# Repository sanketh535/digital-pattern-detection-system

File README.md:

DIGITAL PATTERN DETECTION SYSTEM USING SEQUENTIAL LOGIC (1011)

PROJECT OVERVIEW

This project involves the design and implementation of a digital pattern detection system using sequential logic circuits. The system is designed to detect the assigned 4-bit binary sequence 1011.

The complete system consists of three main sections:

1. Random Pattern Generator – Generates 4-bit binary patterns.
2. PISO Shift Register – Loads parallel data and converts it into a serial data stream.
3. FSM Pattern Detector – Detects the binary sequence 1011 from the incoming serial data.

The three sections are integrated using a common clock signal to perform sequential pattern detection.

SYSTEM ARCHITECTURE

1. Random Pattern Generator
2. Parallel-In Serial-Out (PISO) Shift Register
3. Finite State Machine (FSM) Pattern Detector
4. Complete Integrated Pattern Detection System

TOOLS AND TECHNOLOGIES

- Proteus – Circuit design and simulation
- KiCad – PCB design
- Sequential Logic Circuits
- Shift Registers
- Finite State Machines (FSM)

REPOSITORY CONTENTS

Proteus:
- Complete integrated system simulation
- Random Pattern Generator simulation
- PISO Shift Register simulation
- FSM Pattern Detector simulation

KiCad:
- Random Pattern Generator PCB design
- PISO Shift Register PCB design
- FSM Pattern Detector PCB design

Images:
- KiCad 3D PCB design views
- Photographs of the three fabricated PCBs

Documentation:
- Project assignment report

PCB DESIGN AND FABRICATION

PCB layouts were designed using KiCad for all three sections of the system. Three PCBs were subsequently fabricated based on the designs.

Note: The fabricated PCBs are bare boards, and electronic components have not yet been mounted.

KEY LEARNING OUTCOMES

- Digital system design using sequential logic
- Shift register design and operation
- Finite State Machine design for sequence detection
- Circuit simulation using Proteus
- PCB layout design using KiCad
- Practical experience in PCB fabrication

PROJECT TEAM

This project was completed collaboratively as part of an academic assignment.

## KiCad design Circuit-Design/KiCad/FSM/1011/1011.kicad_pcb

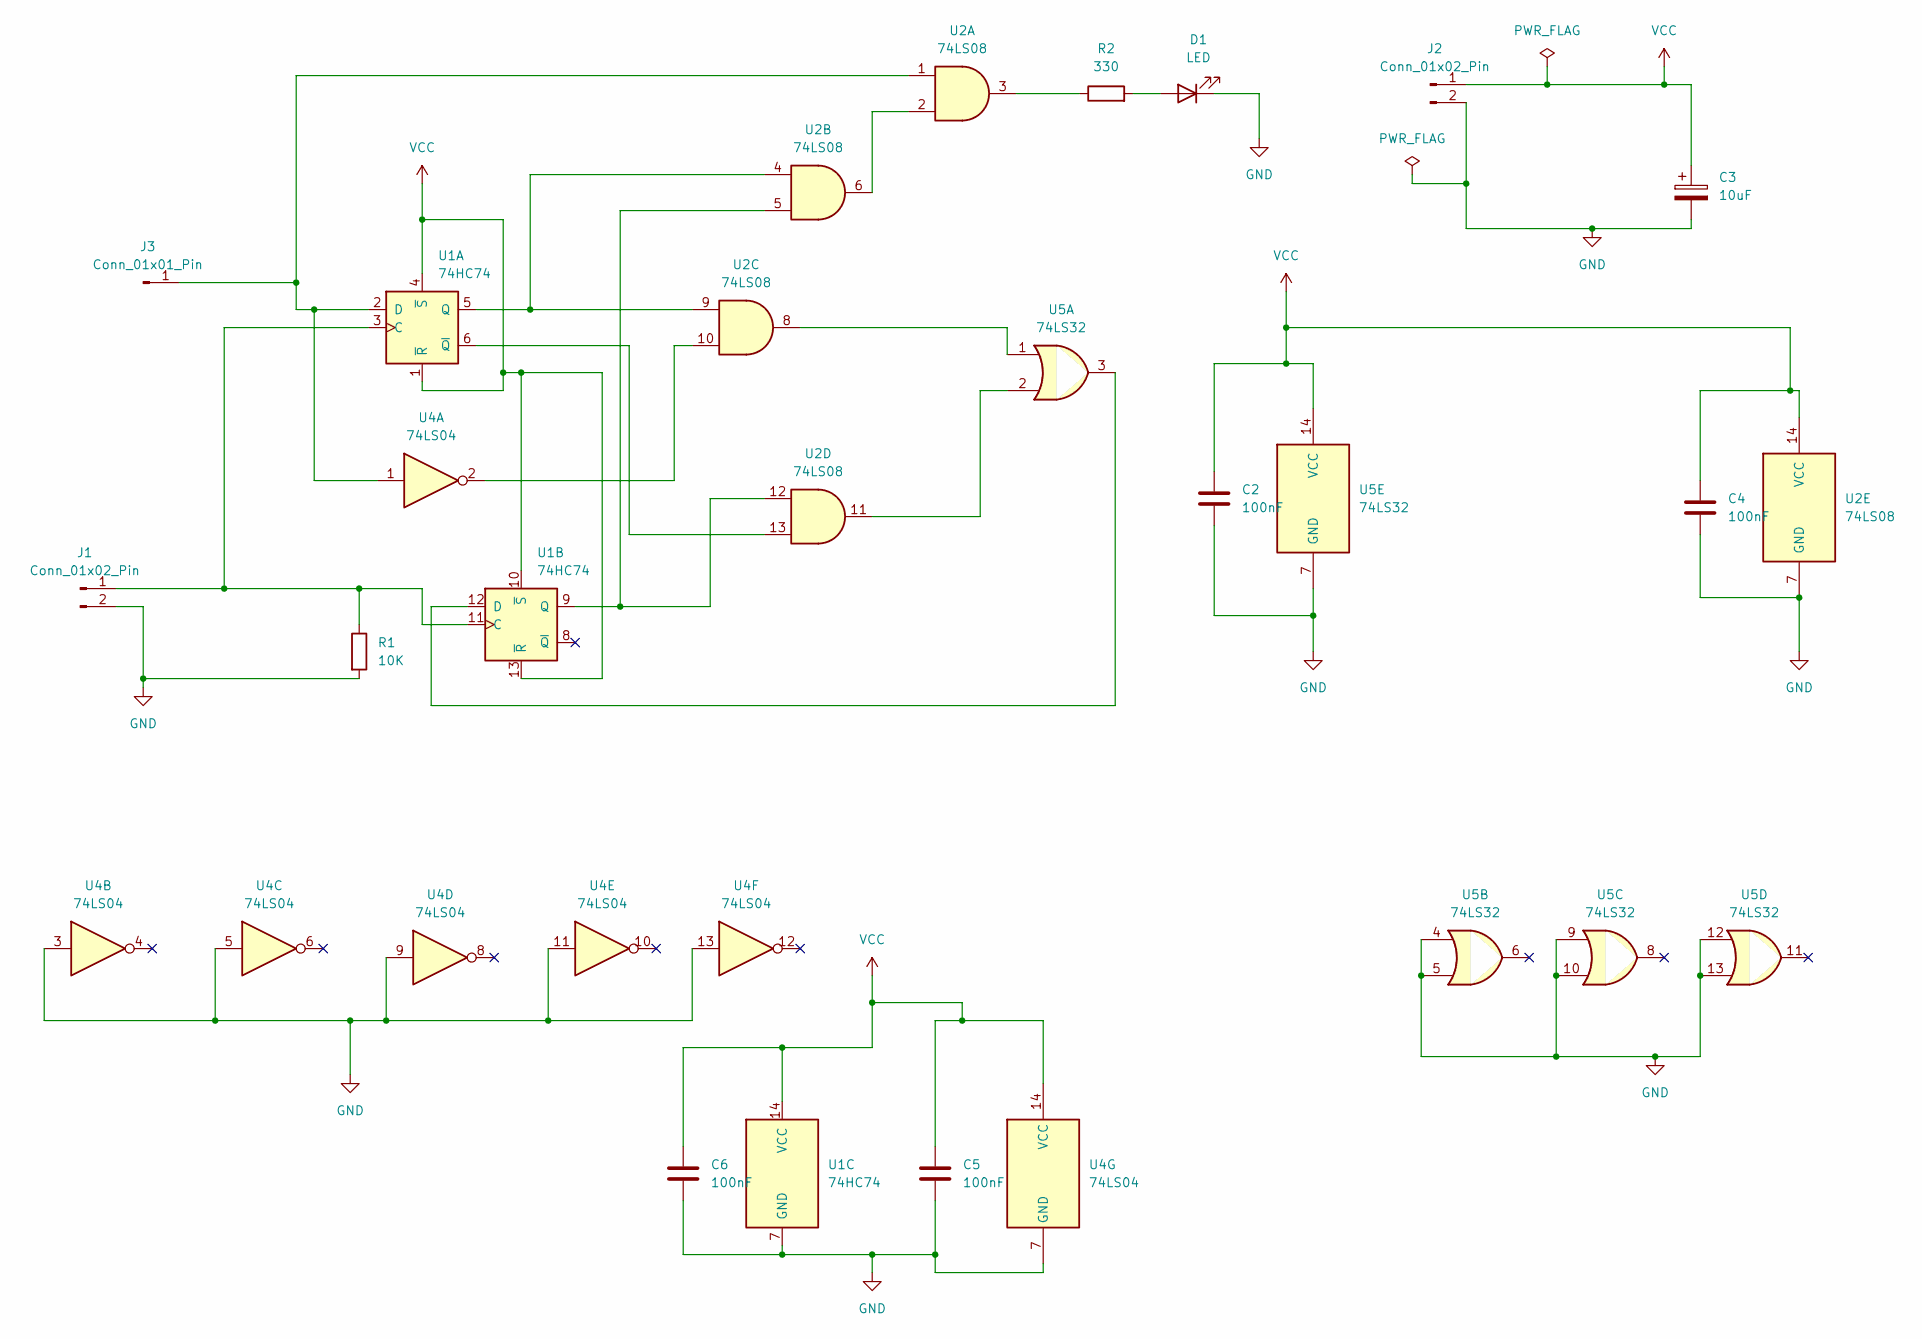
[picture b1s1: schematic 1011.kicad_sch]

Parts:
C2, C4, C5, C6: 100nF; C_Disc_D5.0mm_W2.5mm_P5.00mm
C3: 10uF; CP_Radial_D5.0mm_P2.00mm
D1: LED; LED_D5.0mm
J1, J2: Conn_01x02_Pin; PinHeader_1x02_P2.54mm_Vertical
J3: Conn_01x01_Pin; PinHeader_1x01_P2.54mm_Vertical
R1: 10K; R_Axial_DIN0207_L6.3mm_D2.5mm_P7.62mm_Horizontal
R2: 330; R_Axial_DIN0207_L6.3mm_D2.5mm_P7.62mm_Horizontal
U1: 74HC74; DIP-14_W7.62mm
U2: 74LS08; DIP-14_W7.62mm
U4: 74LS04; DIP-14_W7.62mm
U5: 74LS32; DIP-14_W7.62mm

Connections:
GND: C2.2, C3.2, C4.2, C5.2, C6.2, D1.1 (K), J1.2, J2.2, R1.2, U1.7 (GND), U2.7 (GND), U4.3, U4.5, U4.7 (GND), U4.9, U4.11, U4.13, U5.4, U5.5, U5.7 (GND), U5.9, U5.10, U5.12, U5.13
unnamed: D1.2 (A), R2.2
unnamed: J1.1, R1.1, U1.3 (C), U1.11 (C)
unnamed: J3.1 (Pin_1_1), U1.2 (D), U2.1, U4.1
unnamed: R2.1, U2.3
unnamed: U1.5 (Q), U2.4, U2.9
unnamed: U1.6 (~Q), U2.13
unnamed: U1.12 (D), U5.3
unnamed: U1.9 (Q), U2.5, U2.12
unnamed: U2.2, U2.6
unnamed: U2.8, U5.1
unnamed: U2.10, U4.2
unnamed: U2.11, U5.2
VCC: C2.1, C3.1, C4.1, C5.1, C6.1, J2.1, U1.1 (~R), U1.4 (~S), U1.10 (~S), U1.13 (~R), U1.14 (VCC), U2.14 (VCC), U4.14 (VCC), U5.14 (VCC)

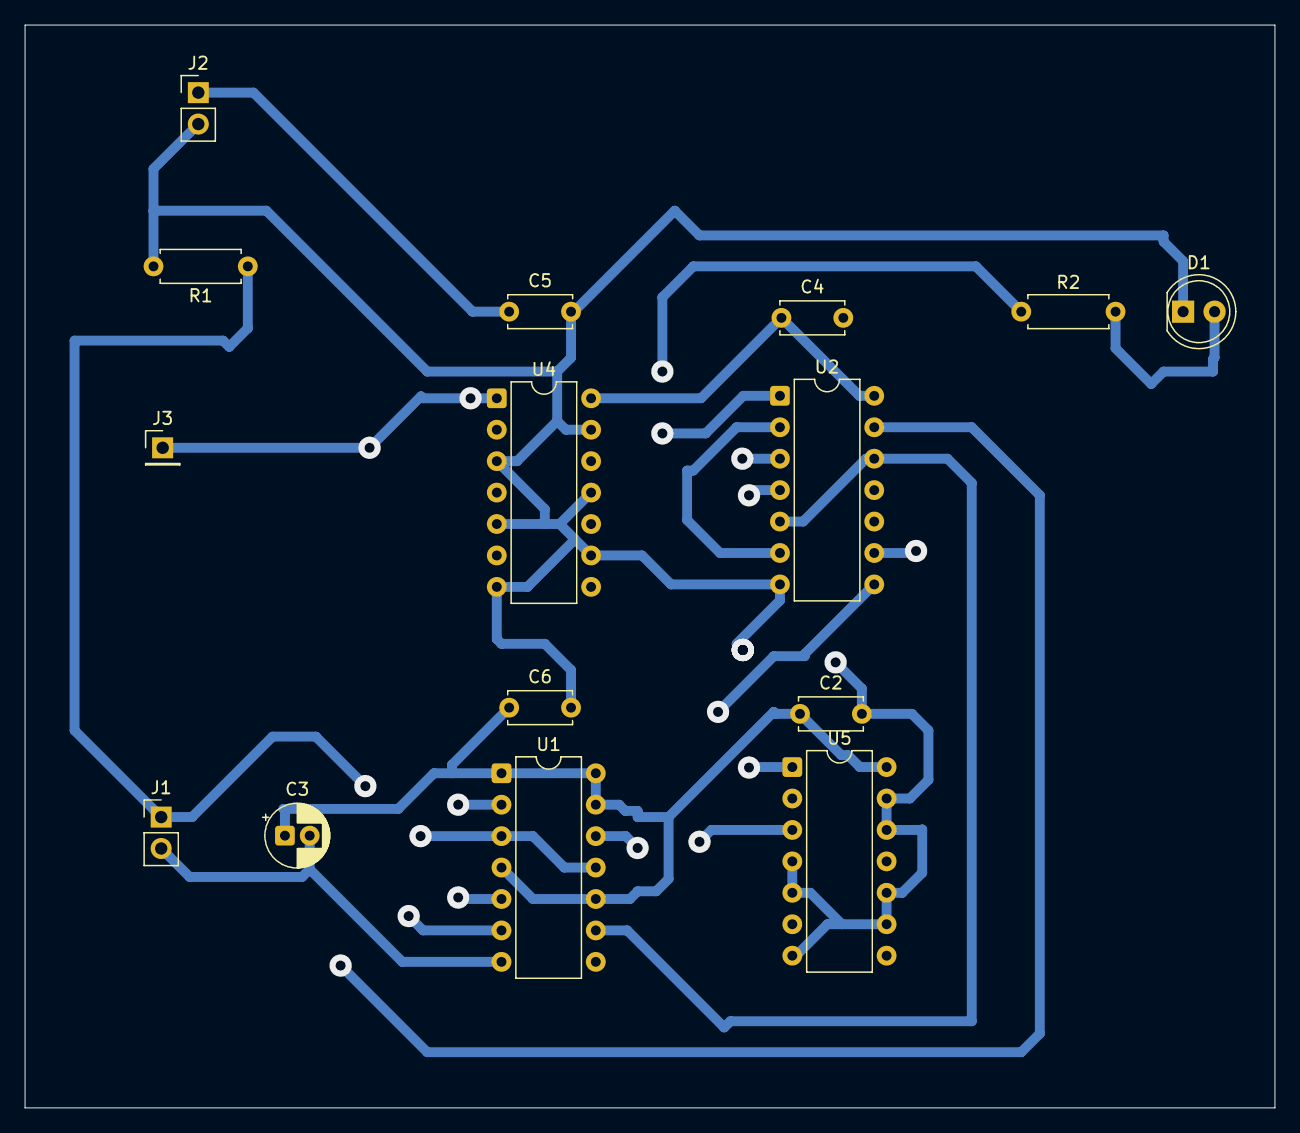
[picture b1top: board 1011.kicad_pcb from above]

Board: 2 copper layers, 101.0 x 87.5 mm, 15 parts (0 on the bottom side), 14 nets.

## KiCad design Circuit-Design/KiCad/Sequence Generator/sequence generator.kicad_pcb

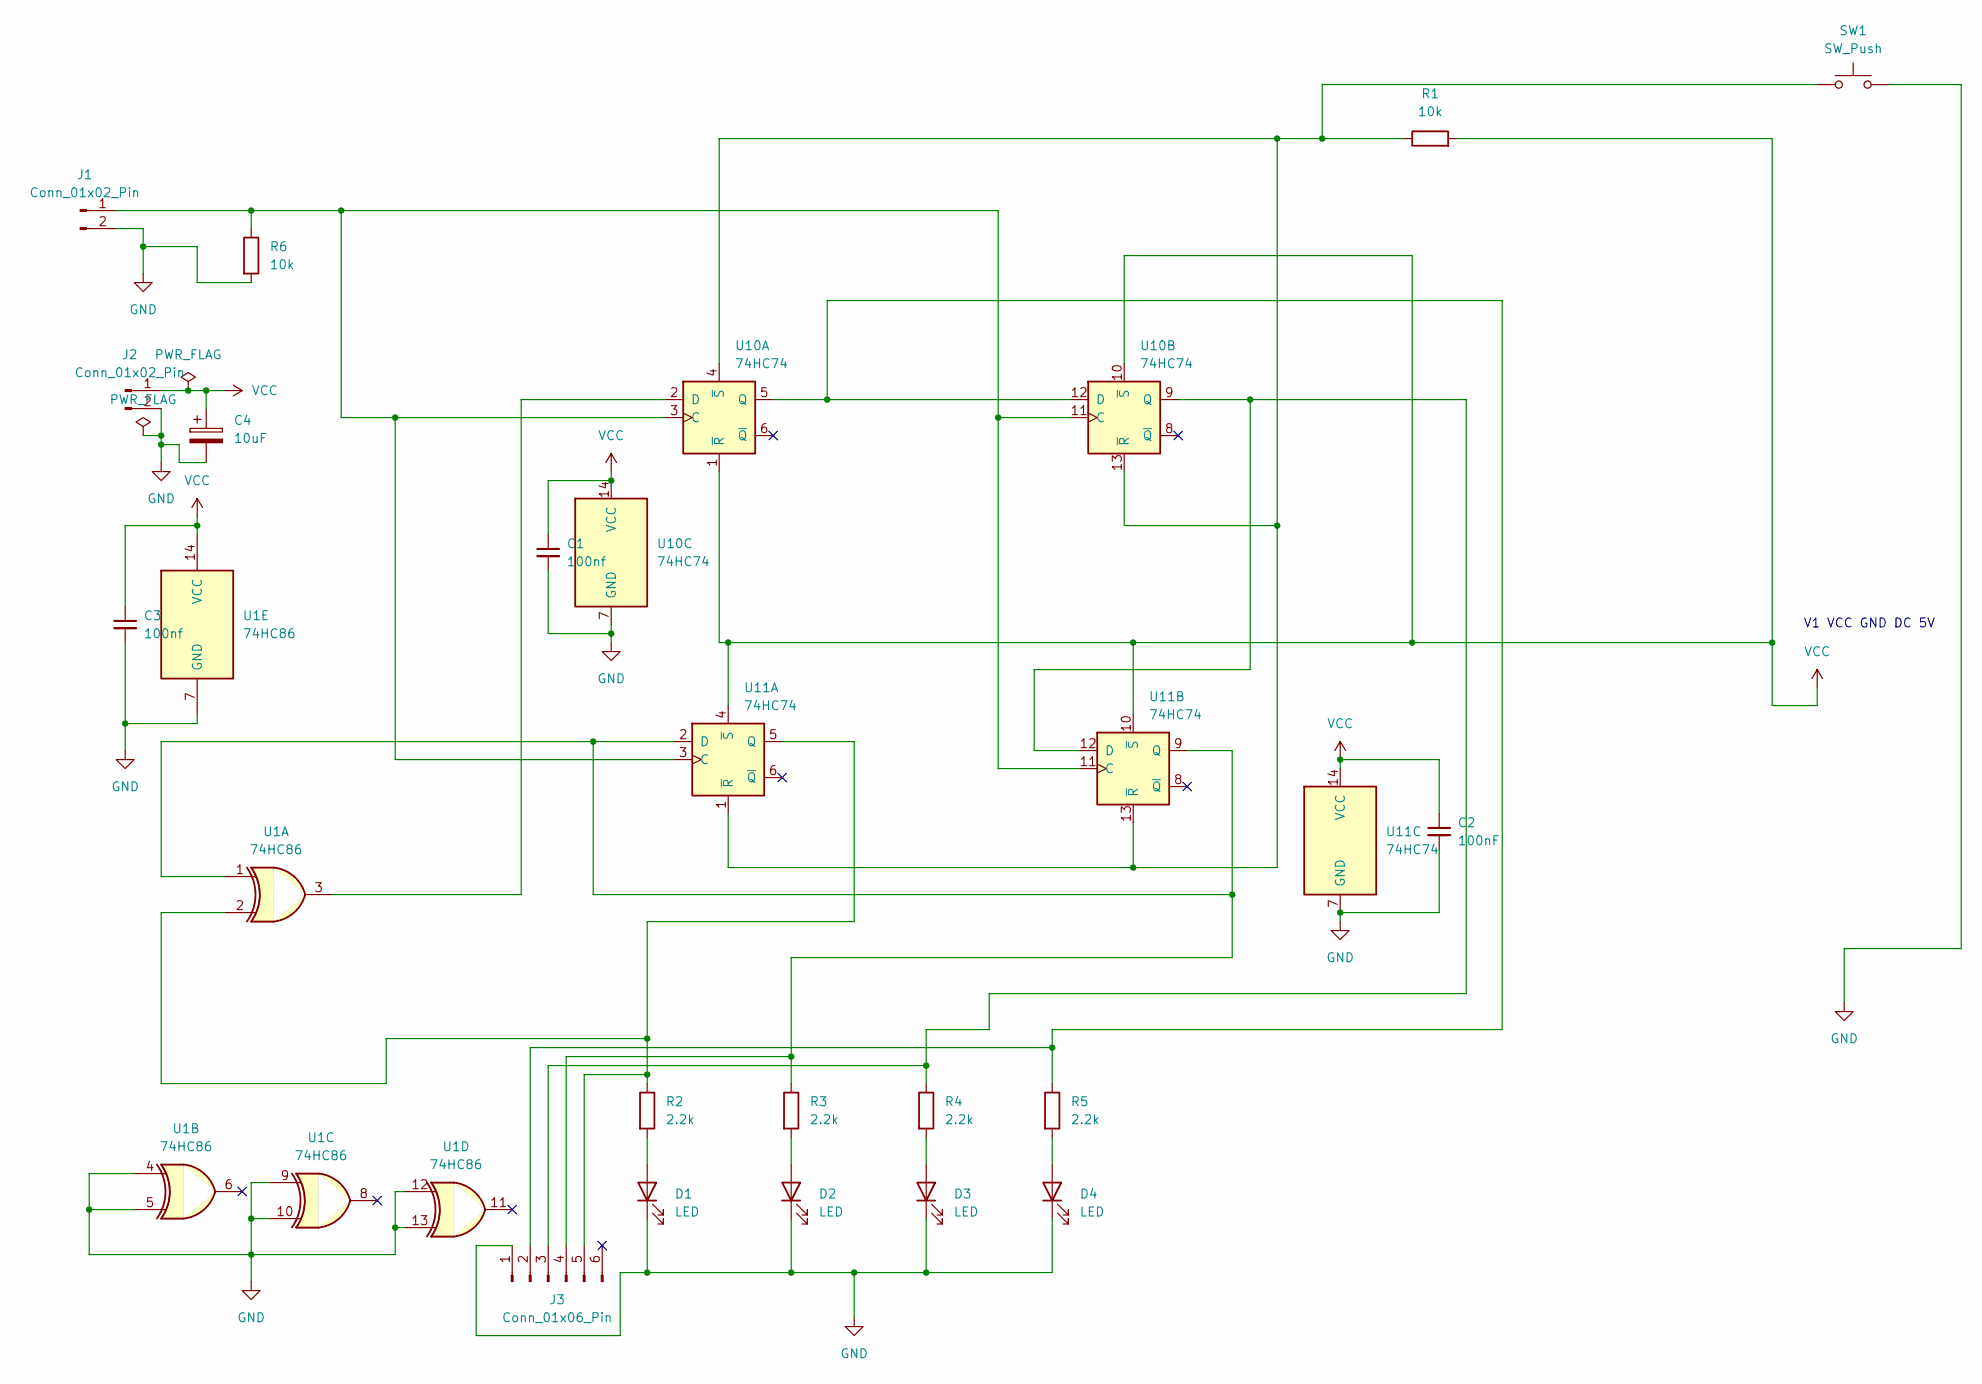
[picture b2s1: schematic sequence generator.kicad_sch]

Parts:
C1, C3: 100nf; C_Disc_D5.0mm_W2.5mm_P5.00mm
C2: 100nF; C_Disc_D5.0mm_W2.5mm_P5.00mm
C4: 10uF; C_Disc_D5.0mm_W2.5mm_P5.00mm
D1, D2, D3, D4: LED; LED_D5.0mm
J1, J2: Conn_01x02_Pin; PinHeader_1x02_P2.54mm_Vertical
J3: Conn_01x06_Pin; PinHeader_1x06_P2.54mm_Vertical
R1, R6: 10k; R_Axial_DIN0207_L6.3mm_D2.5mm_P10.16mm_Horizontal
R2, R3, R4, R5: 2.2k; R_Axial_DIN0207_L6.3mm_D2.5mm_P10.16mm_Horizontal
SW1: SW_Push; SW_PUSH_6mm
U1: 74HC86; DIP-14_W7.62mm
U10, U11: 74HC74; DIP-14_W7.62mm

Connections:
GND: C1.2, C2.2, C3.2, C4.2, D1.1 (K), D2.1 (K), D3.1 (K), D4.1 (K), J1.2, J2.2, J3.1, R6.2, SW1.2, U1.4, U1.5, U1.7 (GND), U1.9, U1.10, U1.12, U1.13, U10.7 (GND), U11.7 (GND)
unnamed: D1.2 (A), R2.2
unnamed: D2.2 (A), R3.2
unnamed: D3.2 (A), R4.2
unnamed: D4.2 (A), R5.2
unnamed: J1.1, R6.1, U10.3 (C), U10.11 (C), U11.3 (C), U11.11 (C)
unnamed: J3.2, R5.1, U10.5 (Q), U10.12 (D)
unnamed: J3.3, R4.1, U10.9 (Q), U11.12 (D)
unnamed: J3.4, R3.1, U1.1, U11.2 (D), U11.9 (Q)
unnamed: J3.5, R2.1, U1.2, U11.5 (Q)
unnamed: U1.3, U10.2 (D)
unnamed: R1.1, SW1.1, U10.4 (~S), U10.13 (~R), U11.1 (~R), U11.13 (~R)
VCC: C1.1, C2.1, C3.1, C4.1, J2.1, R1.2, U1.14 (VCC), U10.1 (~R), U10.10 (~S), U10.14 (VCC), U11.4 (~S), U11.10 (~S), U11.14 (VCC)

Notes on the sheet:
V1 VCC GND DC 5V

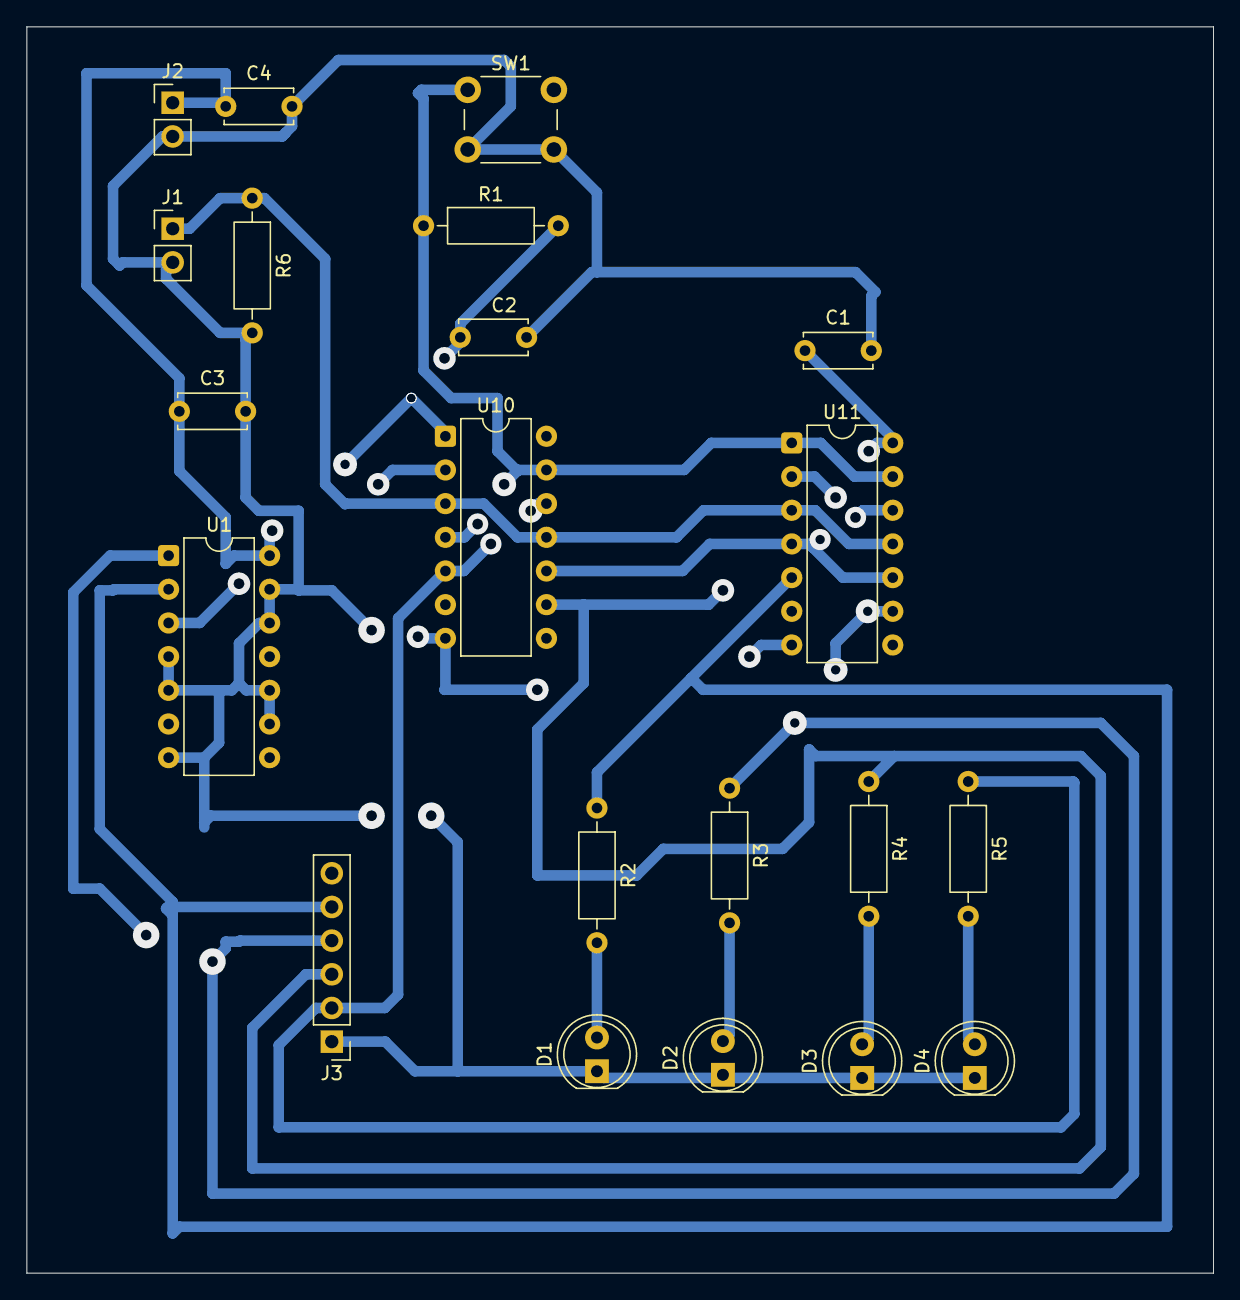
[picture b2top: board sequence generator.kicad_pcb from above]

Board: 2 copper layers, 89.5 x 94.0 mm, 21 parts (0 on the bottom side), 13 nets.

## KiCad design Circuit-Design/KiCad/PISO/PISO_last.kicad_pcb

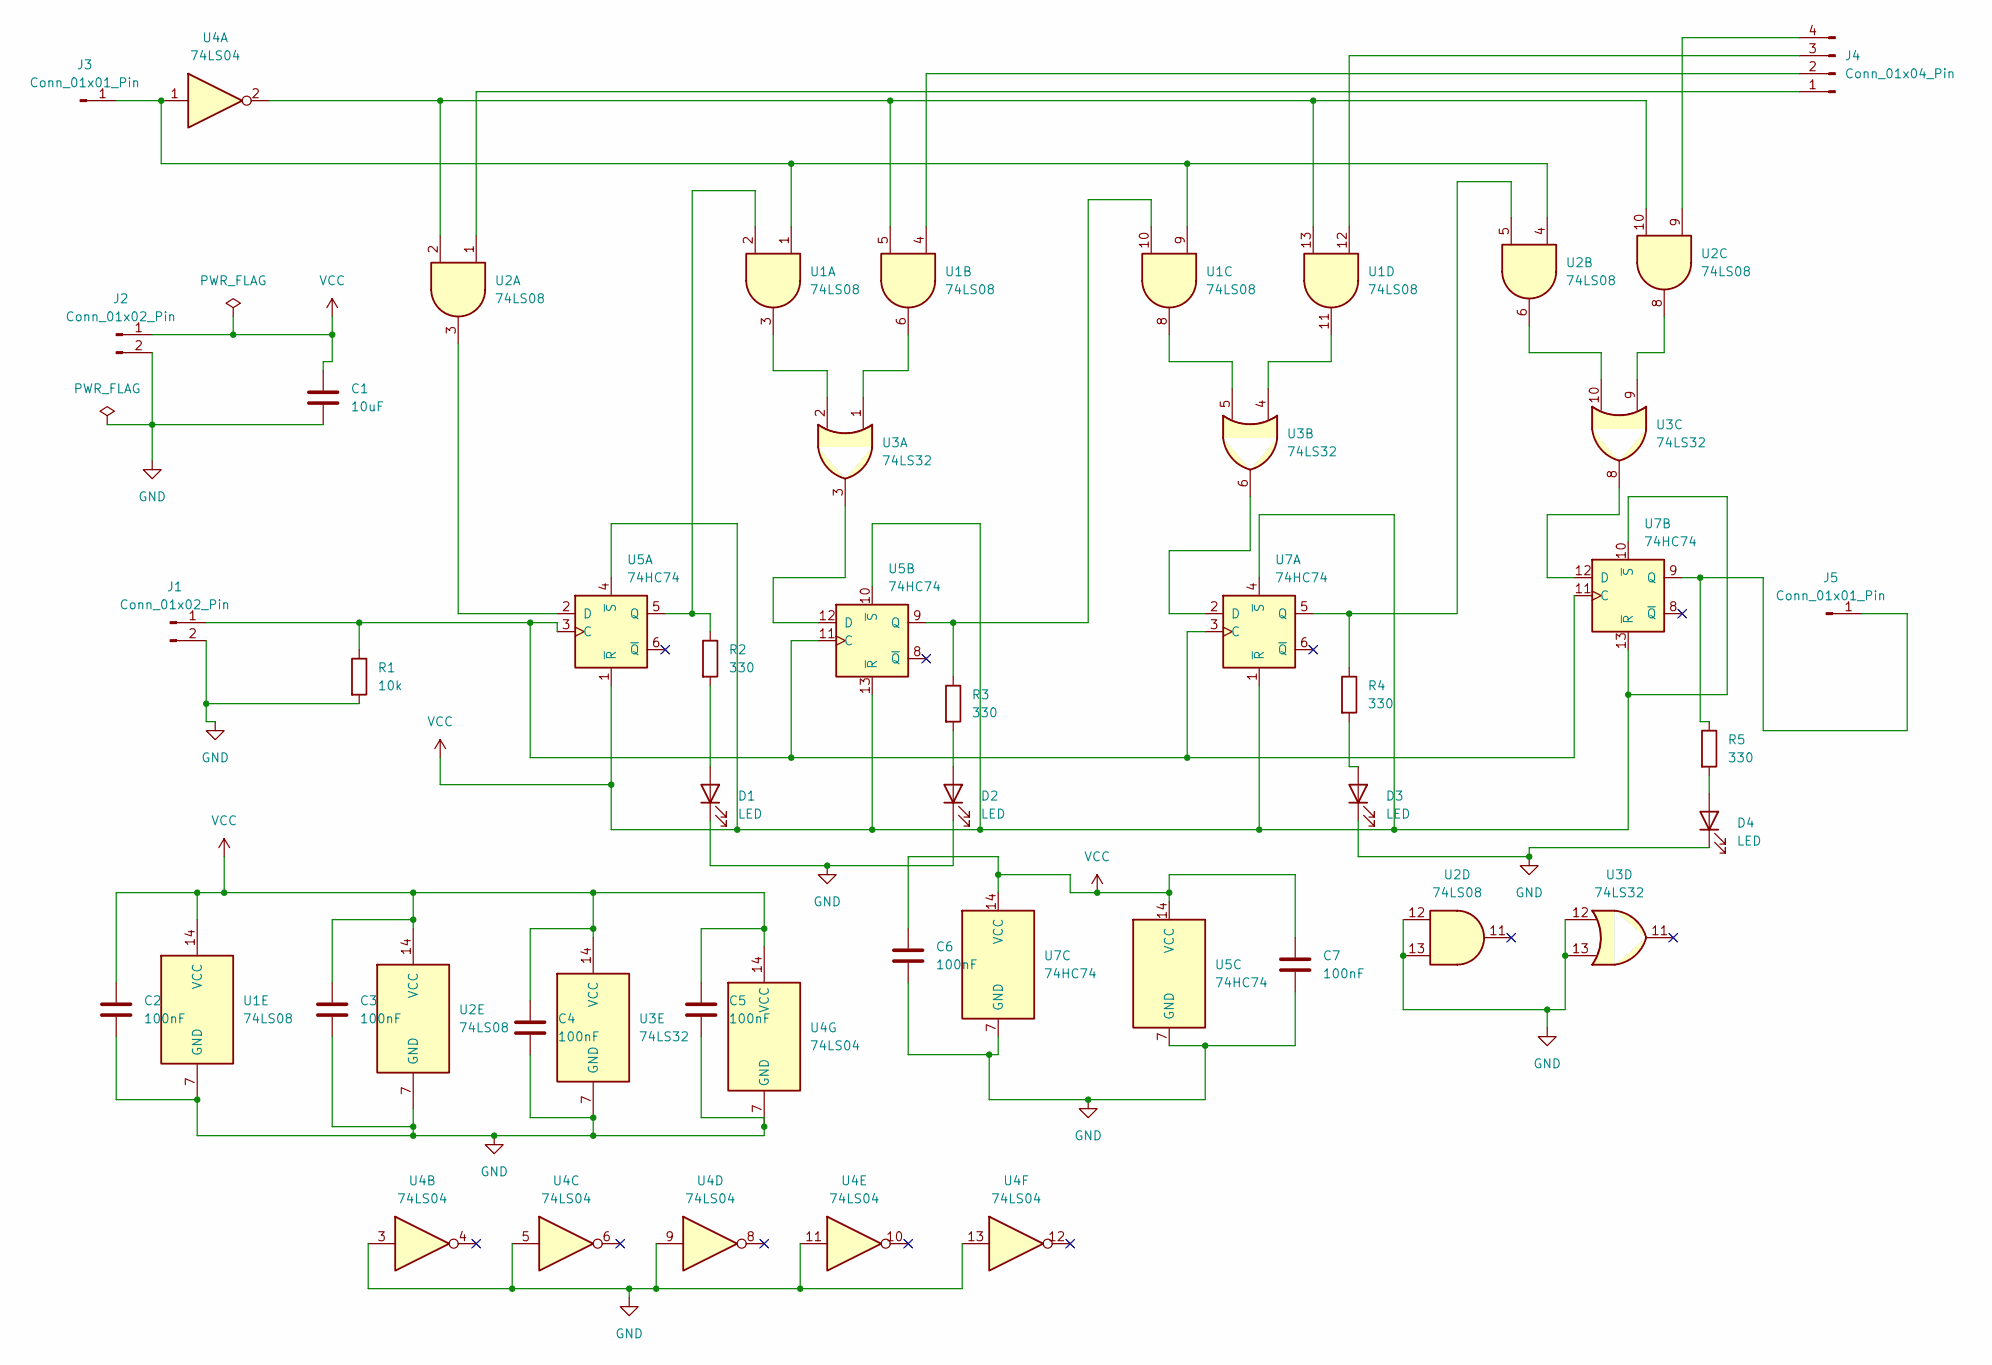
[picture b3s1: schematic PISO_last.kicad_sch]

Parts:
C1: 10uF
C2, C3, C4, C5, C6, C7: 100nF
D1, D2, D3, D4: LED; LED_D5.0mm
J1, J2: Conn_01x02_Pin
J3, J5: Conn_01x01_Pin
J4: Conn_01x04_Pin
R1: 10k
R2, R3, R4, R5: 330; R_Axial_DIN0207_L6.3mm_D2.5mm_P7.62mm_Horizontal
U1, U2: 74LS08
U3: 74LS32
U4: 74LS04
U5, U7: 74HC74

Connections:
GND: C1.2, C2.2, C3.2, C4.2, C5.2, C6.2, C7.2, D1.1 (K), D2.1 (K), D3.1 (K), D4.1 (K), J1.2, J2.2, R1.2, U1.7 (GND), U2.7 (GND), U2.12, U2.13, U3.7 (GND), U3.12, U3.13, U4.3, U4.5, U4.7 (GND), U4.9, U4.11, U4.13, U5.7 (GND), U7.7 (GND)
unnamed: D1.2 (A), R2.2
unnamed: D2.2 (A), R3.2
unnamed: D3.2 (A), R4.2
unnamed: D4.2 (A), R5.2
unnamed: J1.1, R1.1, U5.3 (C), U5.11 (C), U7.3 (C), U7.11 (C)
unnamed: J3.1 (Pin_1_1), U1.1, U1.9, U2.4, U4.1
unnamed: J4.1, U2.1
unnamed: J4.2, U1.4
unnamed: J4.3, U1.12
unnamed: J4.4, U2.9
unnamed: J5.1 (Pin_1_1), R5.1, U7.9 (Q)
unnamed: U1.3, U3.2
unnamed: U1.6, U3.1
unnamed: U1.8, U3.5
unnamed: U1.11, U3.4
unnamed: U1.5, U1.13, U2.2, U2.10, U4.2
unnamed: U2.6, U3.10
unnamed: U2.8, U3.9
unnamed: U2.3, U5.2 (D)
unnamed: R2.1, U1.2, U5.5 (Q)
unnamed: U3.3, U5.12 (D)
unnamed: R3.1, U1.10, U5.9 (Q)
unnamed: U3.6, U7.2 (D)
unnamed: R4.1, U2.5, U7.5 (Q)
unnamed: U3.8, U7.12 (D)
VCC: C1.1, C2.1, C3.1, C4.1, C5.1, C6.1, C7.1, J2.1, U1.14 (VCC), U2.14 (VCC), U3.14 (VCC), U4.14 (VCC), U5.1 (~R), U5.4 (~S), U5.10 (~S), U5.13 (~R), U5.14 (VCC), U7.1 (~R), U7.4 (~S), U7.10 (~S), U7.13 (~R), U7.14 (VCC)

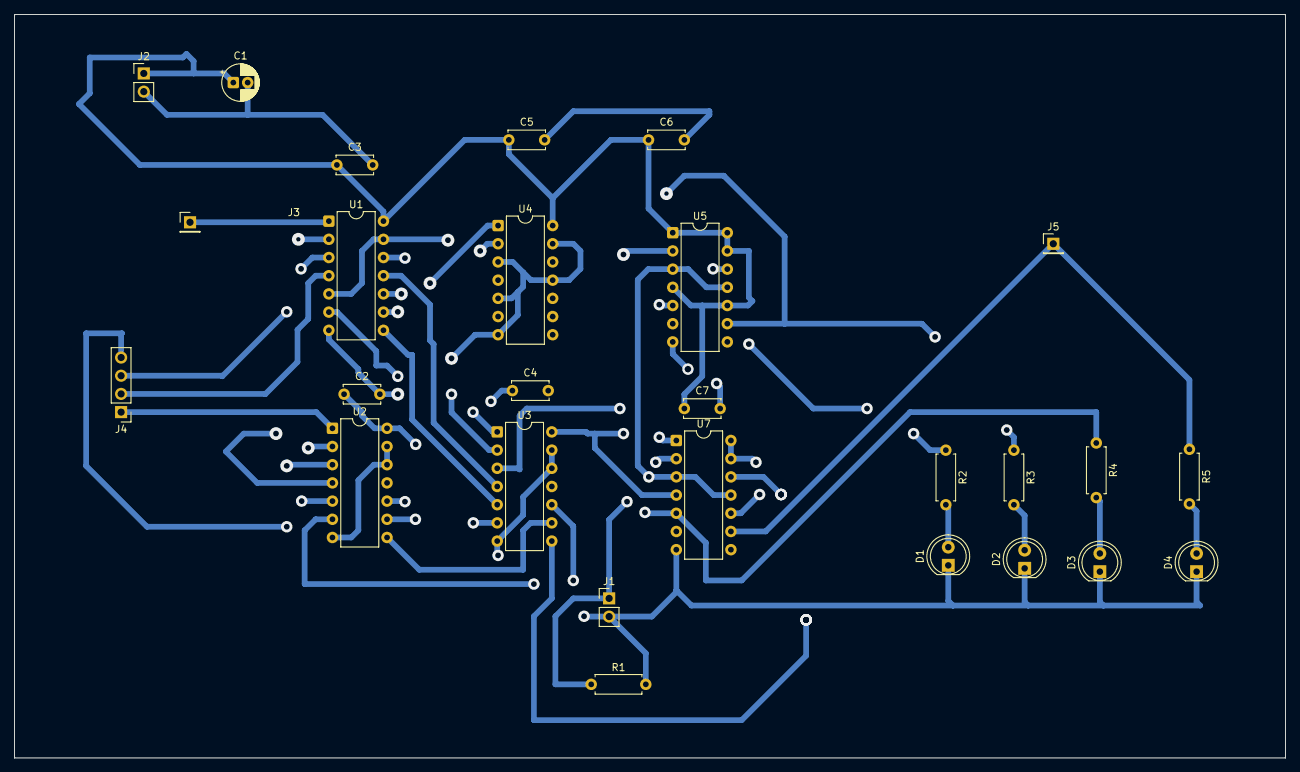
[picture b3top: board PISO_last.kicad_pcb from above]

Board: 2 copper layers, 177.4 x 103.8 mm, 27 parts (0 on the bottom side), 27 nets.
